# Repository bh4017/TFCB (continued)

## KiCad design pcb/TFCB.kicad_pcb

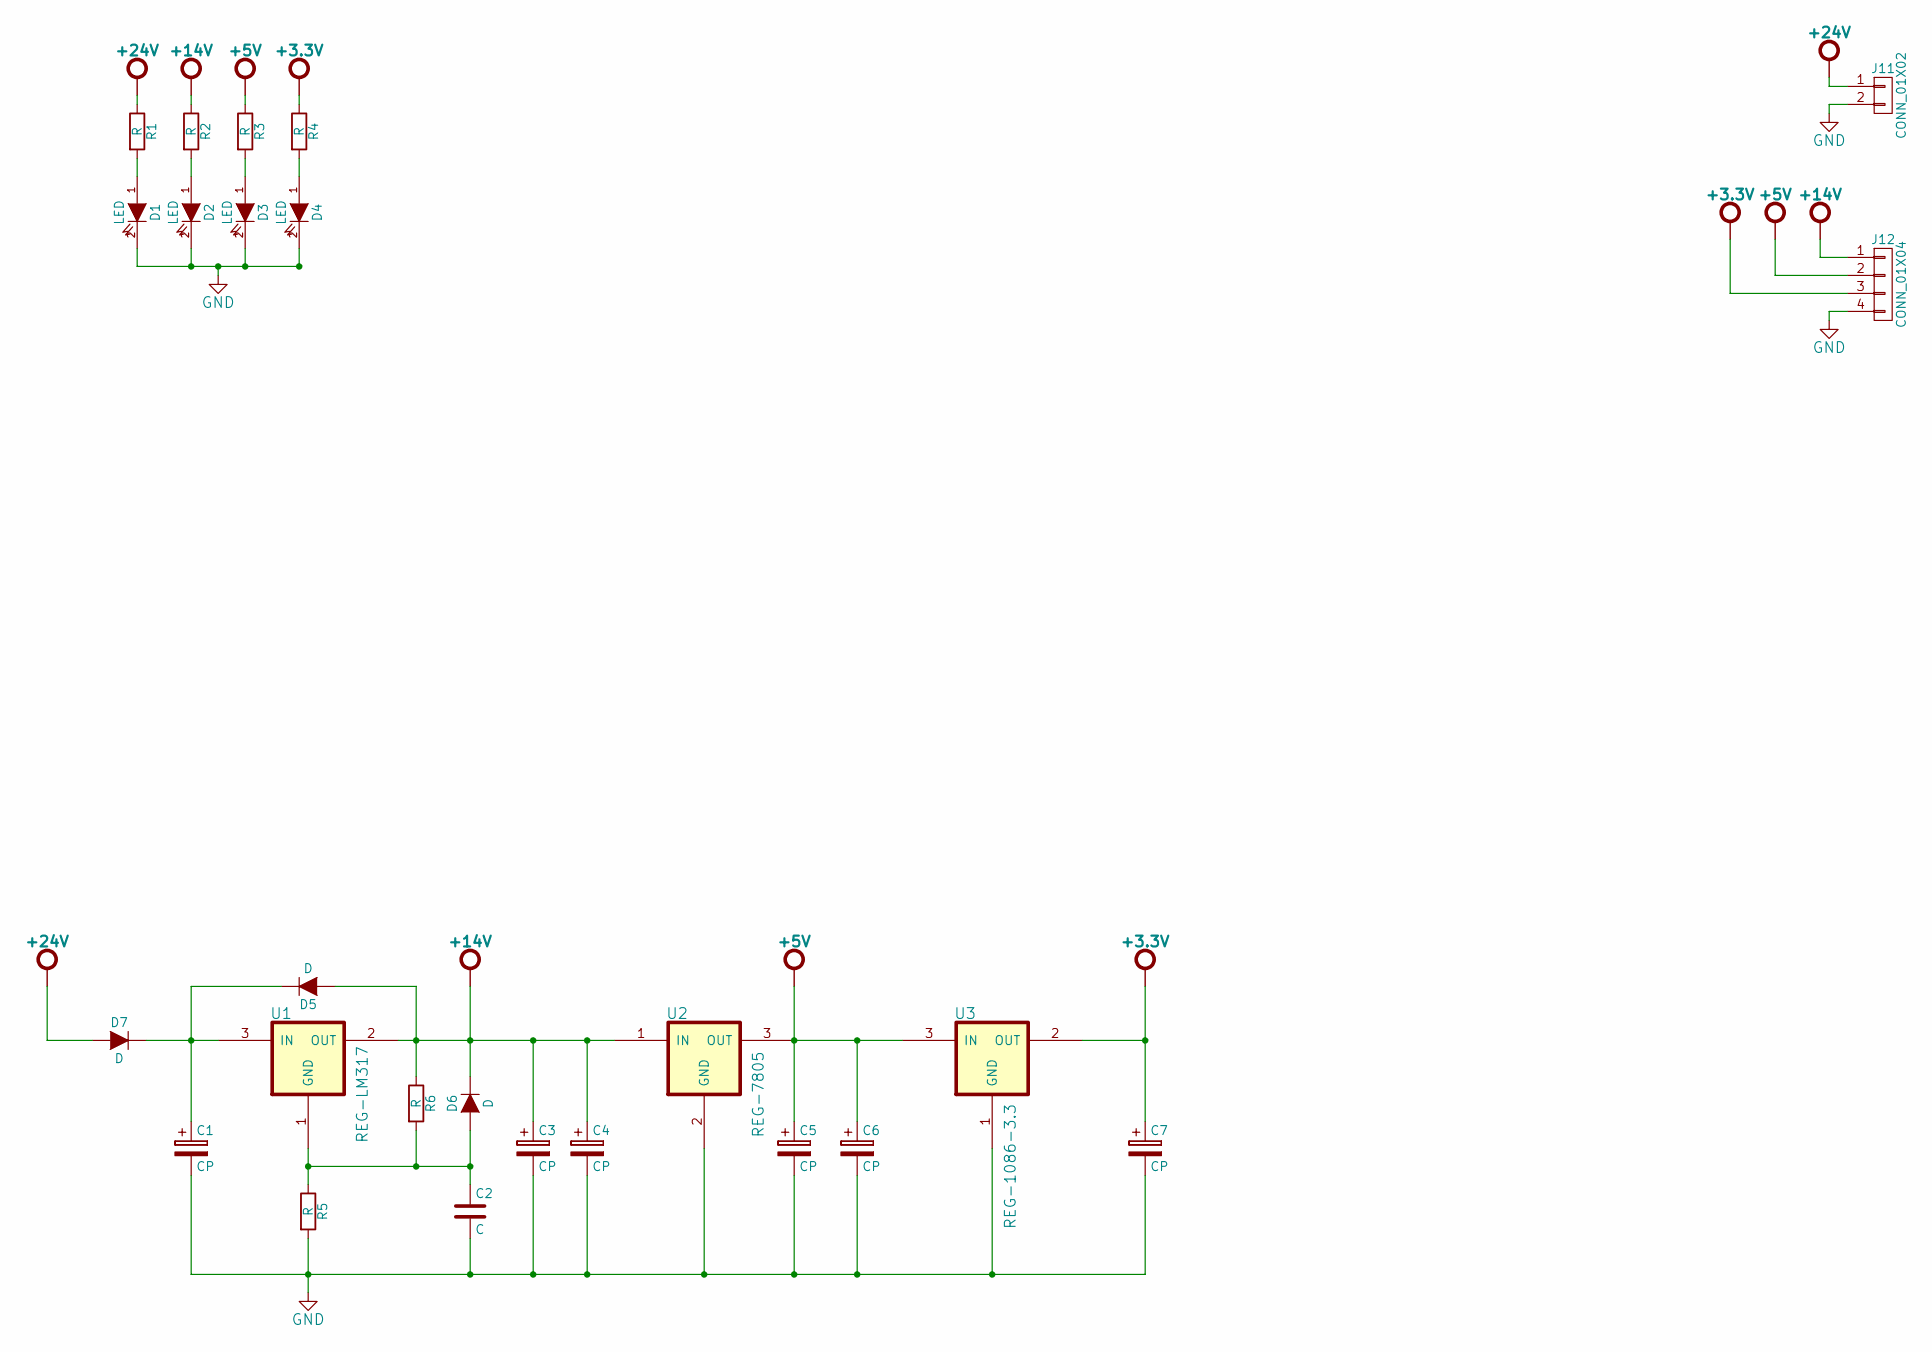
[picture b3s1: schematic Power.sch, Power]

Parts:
C1, C3, C4, C5, C6, C7: CP; TantalC_SizeA_EIA-3216_HandSoldering
C2: C; C_1206_HandSoldering
D1, D2, D3, D4: LED; Diode_LED_5mm_round_vertical
D5, D6: D; Diode-SMB_Handsoldering
D7: D; DO-214AB_Handsoldering
J11: CONN_01X02; Weidmuller-SL-5.08-Vertical-2Pole
J12: CONN_01X04; Weidmuller-SL-5.08-Vertical-4Pole
R1, R2, R3, R4, R5, R6: R; R_0805_HandSoldering
U1: REG-LM317; TO-263-with-copper-heatsink
U2: REG-7805; TO-263-with-copper-heatsink
U3: REG-1086-3.3; TO-263

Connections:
+3.3V: C7.1, J12.3, R4.1, U3.2 (OUT); also elsewhere on the board
+5V: C5.1, C6.1, J12.2, R3.1, U2.3 (OUT), U3.3 (IN)
+14V: C3.1, C4.1, D5.1 (A), D6.2 (K), J12.1, R2.1, R6.1, U1.2 (OUT), U2.1 (IN)
+24V: D7.1 (A), J11.1, R1.1
GND: C1.2, C2.2, C3.2, C4.2, C5.2, C6.2, C7.2, D1.2 (K), D2.2 (K), D3.2 (K), D4.2 (K), J11.2, J12.4, R5.2, U2.2 (GND), U3.1 (GND); also elsewhere on the board
unnamed: C1.1, D5.2 (K), D7.2 (K), U1.3 (IN)
unnamed: C2.1, D6.1 (A), R5.1, R6.2, U1.1 (GND)
unnamed: D1.1 (A), R1.2
unnamed: D2.1 (A), R2.2
unnamed: D3.1 (A), R3.2
unnamed: D4.1 (A), R4.2

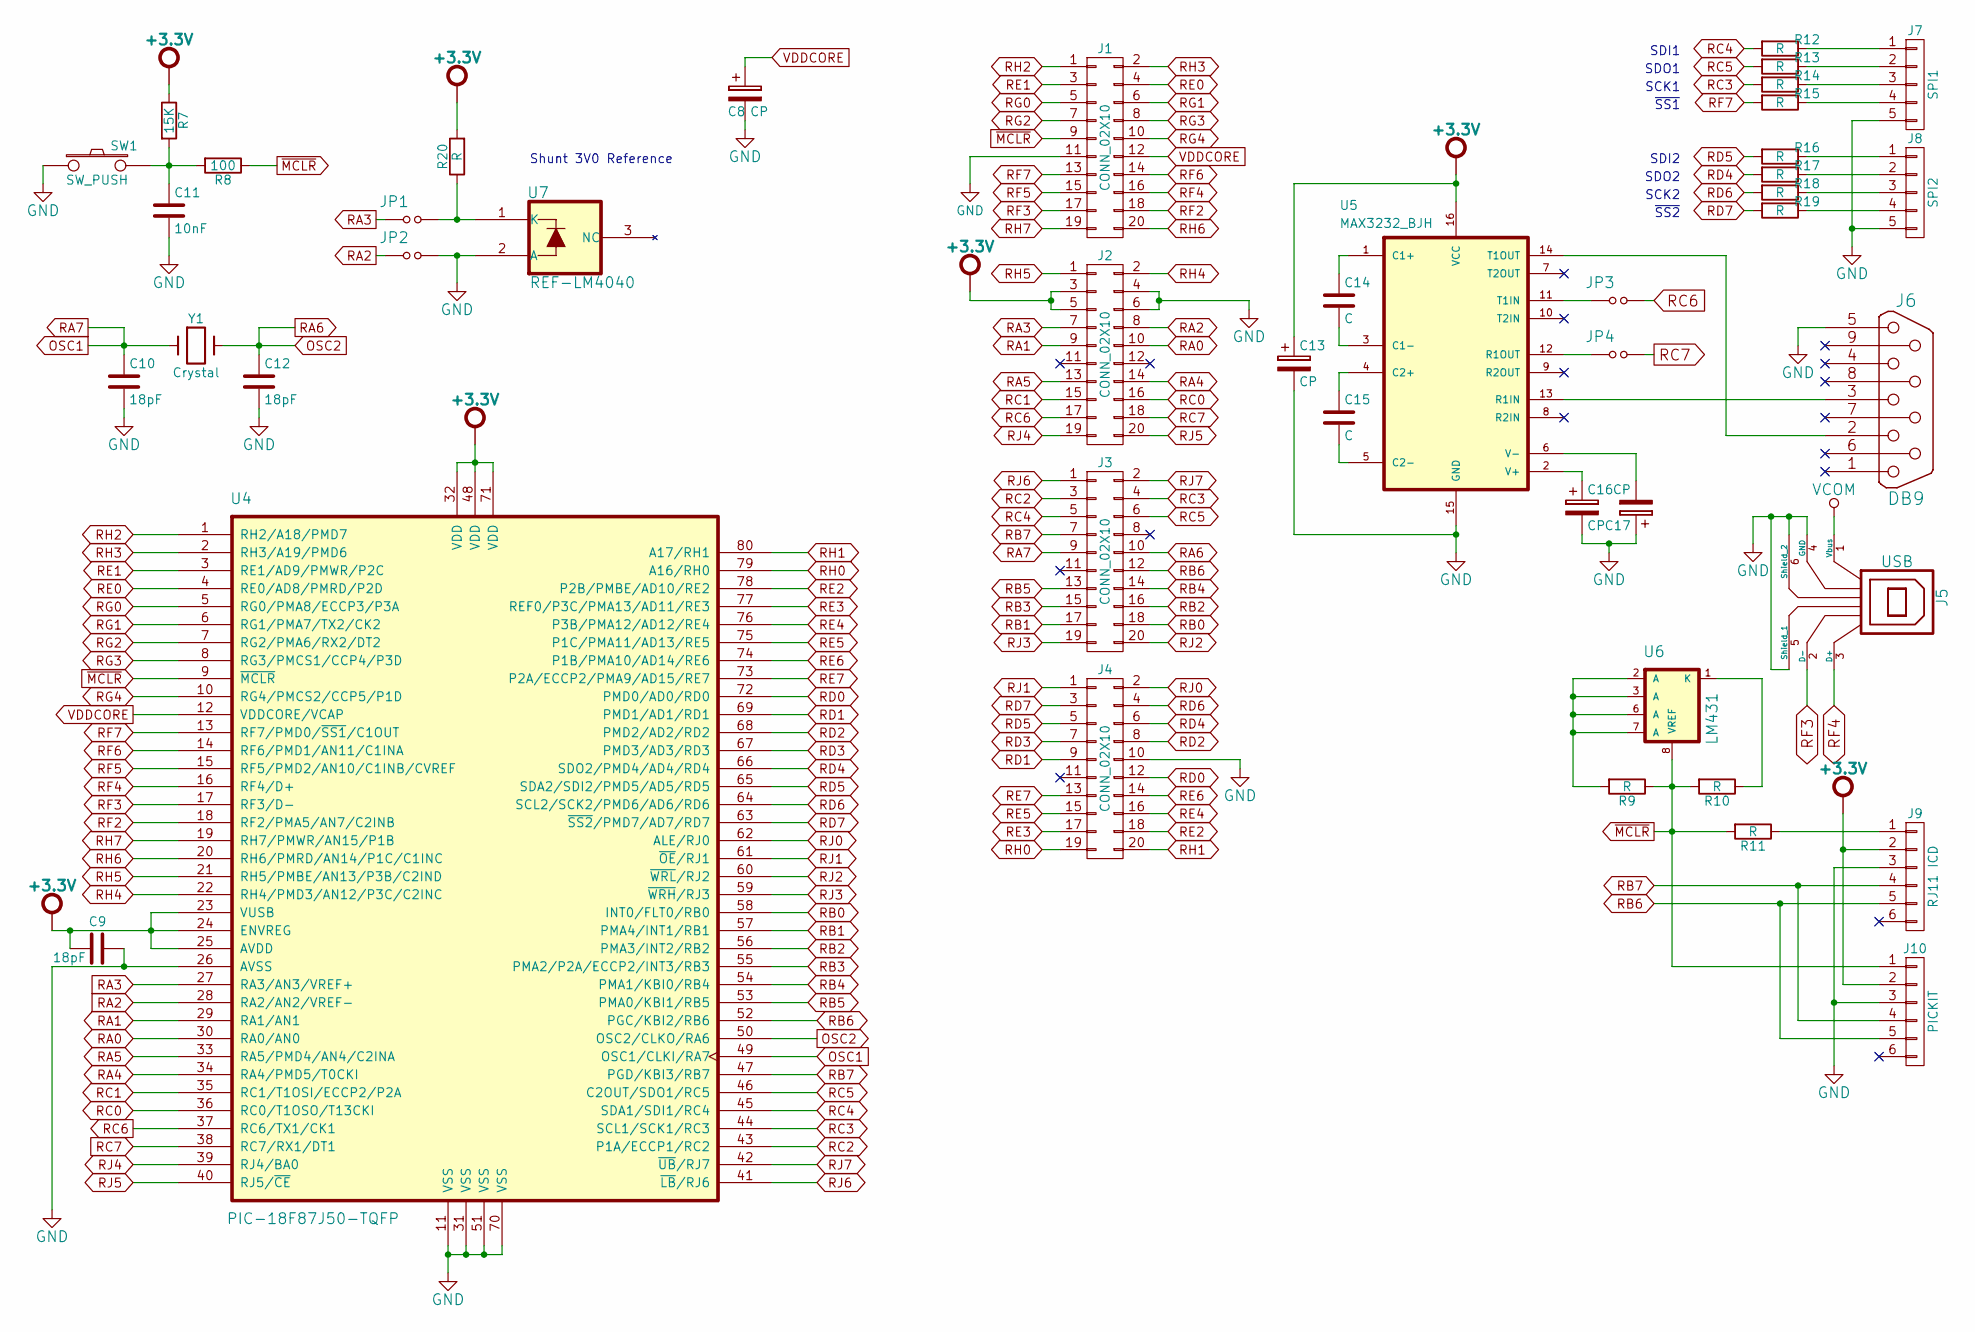
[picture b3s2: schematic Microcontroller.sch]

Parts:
C8, C13, C16, C17: CP; TantalC_SizeA_EIA-3216_HandSoldering
C9, C10, C12: 18pF; C_0805_HandSoldering
C11: 10nF; C_0805_HandSoldering
C14, C15: C; C_1206_HandSoldering
J1, J2, J3, J4: CONN_02X10; RCPT-2row-2.54mm-20way
J5: USB; USB2.0-B-RCPT-SMT-TEConn-1734346-1
J6: DB9; Tyco-DB9-SMT
J7: SPI1; Weidmuller-SL-5.08-Vertical-5Pole
J8: SPI2; Weidmuller-SL-5.08-Vertical-5Pole
J9: RJ11 ICD; Molex-44144-0005-RJ11-Jack-6Way-SMT
J10: PICKIT; RCPT-1row-2.54mm-6way
JP1, JP2, JP3, JP4: Jumper; jumper-2way-through-hole
R7: 15K; R_0805_HandSoldering
R8: 100; R_0805_HandSoldering
R9, R10, R11, R12, R13, R14, R15, R16, R17, R18, R19, R20: R; R_0805_HandSoldering
SW1: SW_PUSH; PushButton-OMRON-B3FS
U4: PIC-18F87J50-TQFP; TQFP-80_12x12mm_Pitch0.5mm
U5: MAX3232_BJH; SOIC-16_7.5x10.3mm_Pitch1.27mm
U6: LM431; SOIC-8_3.9x4.9mm_Pitch1.27mm
U7: REF-LM4040; SOT-23_Handsoldering
Y1: Crystal; Q_49U3HMS

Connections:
+3.3V: C9.2, C13.1, J2.3, J2.5, J9.2, J10.2, R7.1, R20.2, U4.23 (VUSB), U4.24 (ENVREG), U4.25 (AVDD), U4.32 (VDD), U4.48 (VDD), U4.71 (VDD), U5.16 (VCC); also elsewhere on the board
GND: C8.2, C9.1, C10.2, C11.2, C12.2, C13.2, C16.2, C17.1, J1.11, J2.4, J2.6, J4.10, J5.4 (GND), J5.5 (Shield_1), J5.6 (Shield_2), J6.5, J7.5, J8.5, J9.3, J10.3, JP2.2, SW1.1, U4.11 (VSS), U4.26 (AVSS), U4.31 (VSS), U4.51 (VSS), U4.70 (VSS), U5.15 (GND), U7.2 (A); also elsewhere on the board
unnamed: C11.1, R7.2, R8.2, SW1.2
unnamed: C14.1, U5.1 (C1+)
unnamed: C14.2, U5.3 (C1-)
unnamed: C15.1, U5.4 (C2+)
unnamed: C15.2, U5.5 (C2-)
unnamed: C16.1, U5.2 (V+)
unnamed: C17.2, U5.6 (V-)
unnamed: J6.2, U5.14 (T1OUT)
unnamed: J6.3, U5.13 (R1IN)
unnamed: J7.1, R12.1
unnamed: J7.2, R13.1
unnamed: J7.3, R14.1
unnamed: J7.4, R15.1
unnamed: J8.1, R16.1
unnamed: J8.2, R17.1
unnamed: J8.3, R18.1
unnamed: J8.4, R19.1
unnamed: J9.1, R11.1
unnamed: JP1.2, R20.1, U7.1 (K)
unnamed: JP3.1, U5.11 (T1IN)
unnamed: JP4.1, U5.12 (R1OUT)
unnamed: R9.2, U6.2 (A), U6.3 (A), U6.6 (A), U6.7 (A)
unnamed: R10.1, U6.1 (K)
OSC1: C10.1, J3.9, U4.49 (OSC1/CLKI/RA7), Y1.1
OSC2: C12.1, J3.10, U4.50 (OSC2/CLKO/RA6), Y1.2
RA0: J2.10, U4.30 (RA0/AN0)
RA1: J2.9, U4.29 (RA1/AN1)
RA2: J2.8, JP2.1, U4.28 (RA2/AN2/VREF-)
RA3: J2.7, JP1.1, U4.27 (RA3/AN3/VREF+)
RA4: J2.14, U4.34 (RA4/PMD5/T0CKI)
RA5: J2.13, U4.33 (RA5/PMD4/AN4/C2INA)
RB0: J3.18, U4.58 (INT0/FLT0/RB0)
RB1: J3.17, U4.57 (PMA4/INT1/RB1)
RB2: J3.16, U4.56 (PMA3/INT2/RB2)
RB3: J3.15, U4.55 (PMA2/P2A/ECCP2/INT3/RB3)
RB4: J3.14, U4.54 (PMA1/KBI0/RB4)
RB5: J3.13, U4.53 (PMA0/KBI1/RB5)
RB6: J3.12, J9.5, J10.5, U4.52 (PGC/KBI2/RB6)
RB7: J3.7, J9.4, J10.4, U4.47 (PGD/KBI3/RB7)
RC0: J2.16, U4.36 (RC0/T1OSO/T13CKI)
RC1: J2.15, U4.35 (RC1/T1OSI/ECCP2/P2A)
RC2: J3.3, U4.43 (P1A/ECCP1/RC2)
RC3: J3.4, R14.2, U4.44 (SCL1/SCK1/RC3)
RC4: J3.5, R12.2, U4.45 (SDA1/SDI1/RC4)
RC5: J3.6, R13.2, U4.46 (C2OUT/SDO1/RC5)
RC6: J2.17, JP3.2, U4.37 (RC6/TX1/CK1)
RC7: J2.18, JP4.2, U4.38 (RC7/RX1/DT1)
RD0: J4.12, U4.72 (PMD0/AD0/RD0)
RD1: J4.9, U4.69 (PMD1/AD1/RD1)
RD2: J4.8, U4.68 (PMD2/AD2/RD2)
RD3: J4.7, U4.67 (PMD3/AD3/RD3)
RD4: J4.6, R17.2, U4.66 (SDO2/PMD4/AD4/RD4)
RD5: J4.5, R16.2, U4.65 (SDA2/SDI2/PMD5/AD5/RD5)
RD6: J4.4, R18.2, U4.64 (SCL2/SCK2/PMD6/AD6/RD6)
RD7: J4.3, R19.2, U4.63 (~SS2~/PMD7/AD7/RD7)
RE0: J1.4, U4.4 (RE0/AD8/PMRD/P2D)
RE1: J1.3, U4.3 (RE1/AD9/PMWR/P2C)
RE2: J4.18, U4.78 (P2B/PMBE/AD10/RE2)
RE3: J4.17, U4.77 (REF0/P3C/PMA13/AD11/RE3)
RE4: J4.16, U4.76 (P3B/PMA12/AD12/RE4)
RE5: J4.15, U4.75 (P1C/PMA11/AD13/RE5)
RE6: J4.14, U4.74 (P1B/PMA10/AD14/RE6)
RE7: J4.13, U4.73 (P2A/ECCP2/PMA9/AD15/RE7)
RF2: J1.18, U4.18 (RF2/PMA5/AN7/C2INB)
RF3: J1.17, J5.2 (D-), U4.17 (RF3/D-)
RF4: J1.16, J5.3 (D+), U4.16 (RF4/D+)
RF5: J1.15, U4.15 (RF5/PMD2/AN10/C1INB/CVREF)
RF6: J1.14, U4.14 (RF6/PMD1/AN11/C1INA)
RF7: J1.13, R15.2, U4.13 (RF7/PMD0/~SS1~/C1OUT)
RG0: J1.5, U4.5 (RG0/PMA8/ECCP3/P3A)
RG1: J1.6, U4.6 (RG1/PMA7/TX2/CK2)
RG2: J1.7, U4.7 (RG2/PMA6/RX2/DT2)
RG3: J1.8, U4.8 (RG3/PMCS1/CCP4/P3D)
RG4: J1.10, U4.10 (RG4/PMCS2/CCP5/P1D)
RH0: J4.19, U4.79 (A16/RH0)
RH1: J4.20, U4.80 (A17/RH1)
RH2: J1.1, U4.1 (RH2/A18/PMD7)
RH3: J1.2, U4.2 (RH3/A19/PMD6)
RH4: J2.2, U4.22 (RH4/PMD3/AN12/P3C/C2INC)
RH5: J2.1, U4.21 (RH5/PMBE/AN13/P3B/C2IND)
RH6: J1.20, U4.20 (RH6/PMRD/AN14/P1C/C1INC)
RH7: J1.19, U4.19 (RH7/PMWR/AN15/P1B)
RJ0: J4.2, U4.62 (ALE/RJ0)
RJ1: J4.1, U4.61 (~OE~/RJ1)
RJ2: J3.20, U4.60 (~WRL~/RJ2)
RJ3: J3.19, U4.59 (~WRH~/RJ3)
RJ4: J2.19, U4.39 (RJ4/BA0)
RJ5: J2.20, U4.40 (RJ5/~CE)
RJ6: J3.1, U4.41 (~LB~/RJ6)
RJ7: J3.2, U4.42 (~UB~/RJ7)
VCOM: J5.1 (Vbus)
VDDCORE: C8.1, J1.12, U4.12 (VDDCORE/VCAP)
~MCLR: J1.9, J10.1, R8.1, R9.1, R10.2, R11.2, U4.9 (~MCLR), U6.8 (VREF)

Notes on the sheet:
SDI1
SDO1
SCK1
~SS1
SDI2
SDO2
SCK2
~SS2
Shunt 3V0 Reference

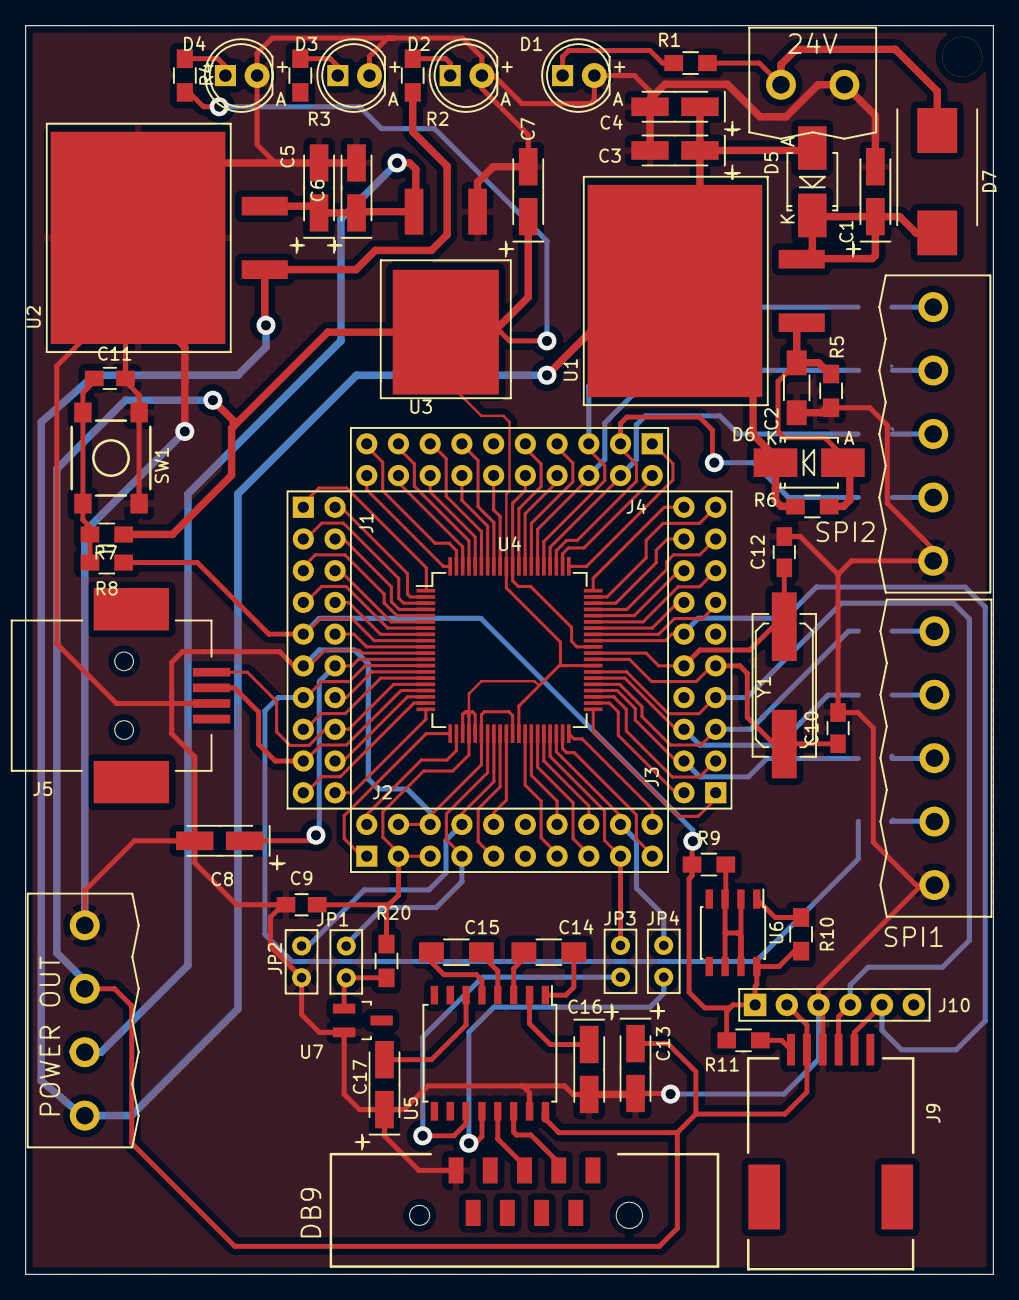
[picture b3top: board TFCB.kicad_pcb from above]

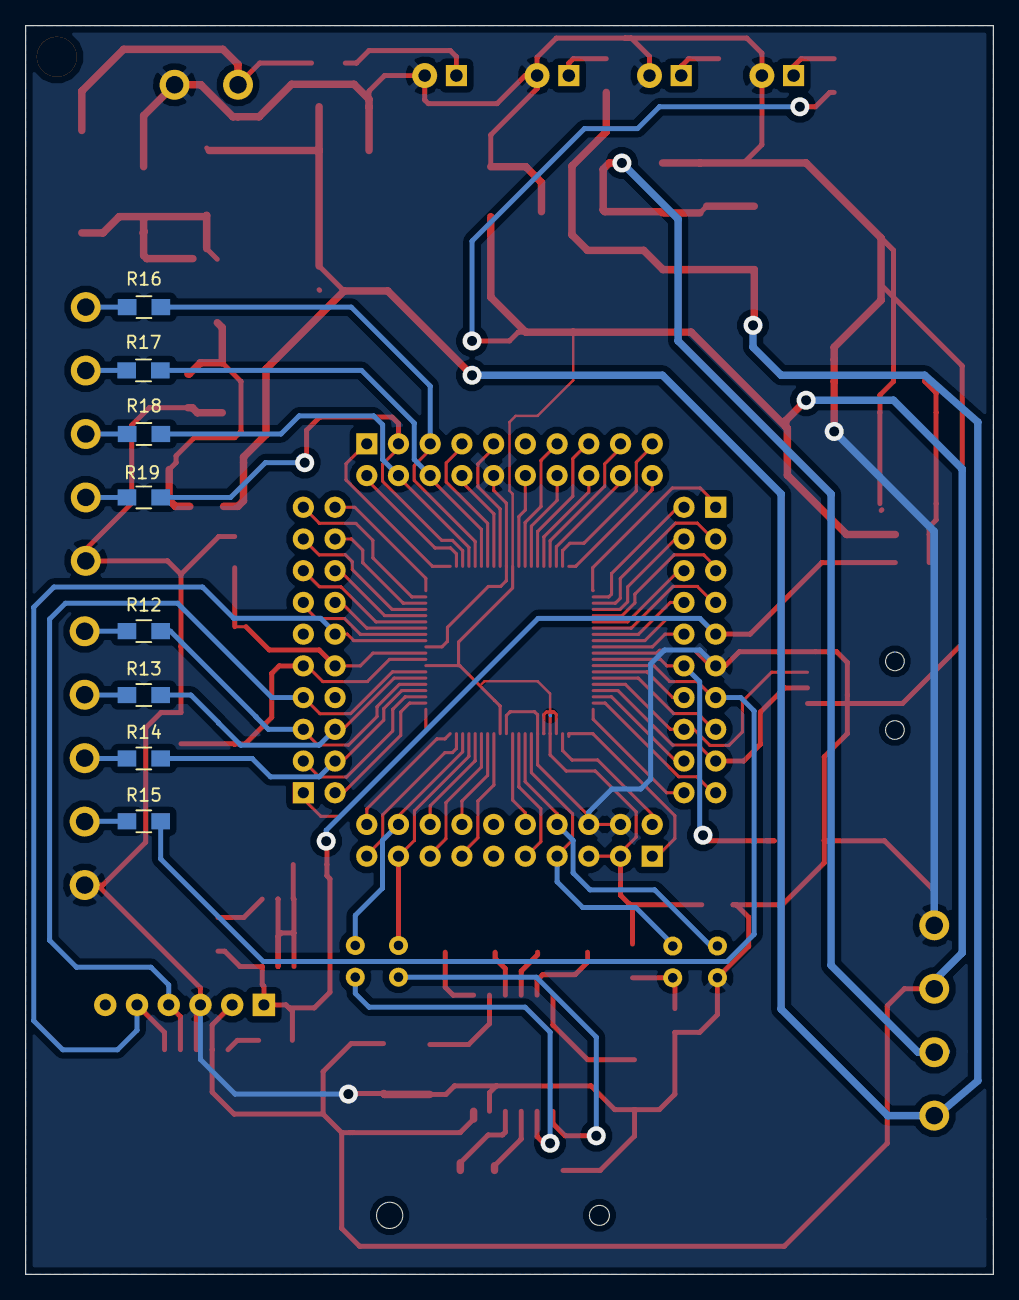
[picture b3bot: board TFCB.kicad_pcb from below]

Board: 2 copper layers, 77.5 x 100.0 mm, 69 parts (8 on the bottom side), 103 nets.

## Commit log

2015-07-21 hoskins.tech
2015-07-25 Added scanner trigger and current sense cct
2015-07-27 latest updates
2015-08-09 More work on TFCB
2015-08-10 More work on the PCB layout
2015-09-02 More work to TFCB
2015-09-02 deleted files which are not required
2015-09-02 added a template hat and created sense hat from this template
2015-10-07 Added new TFCB_HAT template project (for creating new HATS) and an initial commit of a new sense hat.
2015-10-20 Moved power regulators to top side and corrected bad package
2016-02-17 Removed redundant SENSE hat
